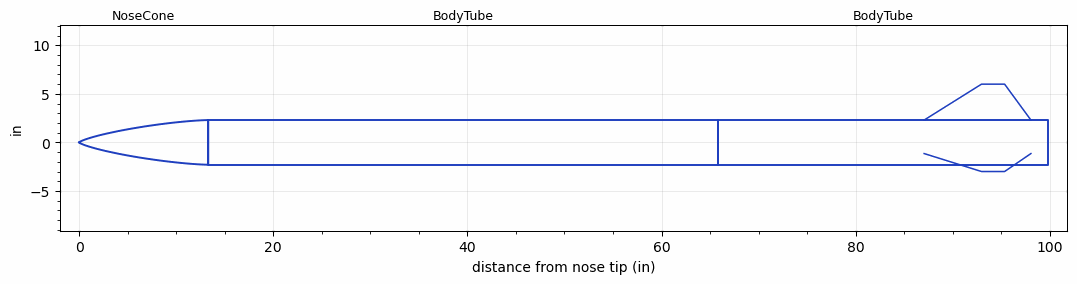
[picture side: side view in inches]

<RASAeroDocument>
 <FileVersion>2</FileVersion>
 <RocketDesign>
  <NoseCone>
   <Length>13.3</Length>
   <Diameter>4.6</Diameter>
   <Shape>Von Karman Ogive</Shape>
   <Location>0</Location>
  </NoseCone>
  <BodyTube>
   <Length>52.5</Length>
   <Diameter>4.6</Diameter>
   <Location>13.3</Location>
  </BodyTube>
  <BodyTube>
   <Length>34</Length>
   <Diameter>4.6</Diameter>
   <RailGuideDiameter>0.5</RailGuideDiameter>
   <RailGuideHeight>0.5</RailGuideHeight>
   <Location>65.8</Location>
   <Fin>
    <Count>3</Count>
    <Chord>11</Chord>
    <Span>3.7</Span>
    <SweepDistance>5.91</SweepDistance>
    <TipChord>2.38</TipChord>
    <Thickness>0.3</Thickness>
    <Location>12.75</Location>
    <AirfoilSection>Subsonic NACA</AirfoilSection>
   </Fin>
  </BodyTube>
  <Surface>Smooth (Zero Roughness)</Surface>
  <ModifiedBarrowman>False</ModifiedBarrowman>
  <Turbulence>False</Turbulence>
  <UseBooster1>False</UseBooster1>
  <UseBooster2>False</UseBooster2>
 </RocketDesign>
 <LaunchSite>
  <Altitude>4593</Altitude>
  <Pressure>25.4</Pressure>
  <RodAngle>6</RodAngle>
  <RodLength>15</RodLength>
  <Temperature>100</Temperature>
  <WindSpeed>0</WindSpeed>
 </LaunchSite>
 <Recovery>
  <Altitude1>1000</Altitude1>
  <Altitude2>1500</Altitude2>
  <DeviceType1>Parachute</DeviceType1>
  <DeviceType2>Parachute</DeviceType2>
  <Event1>True</Event1>
  <Event2>True</Event2>
  <Size1>33</Size1>
  <Size2>120</Size2>
  <EventType1>Apogee</EventType1>
  <EventType2>Altitude</EventType2>
  <CD1>1.33</CD1>
  <CD2>2.2</CD2>
 </Recovery>
 <SimulationList>
  <Simulation>
   <SustainerEngine>L1685-SS  (CTI)</SustainerEngine>
   <SustainerLaunchWt>39</SustainerLaunchWt>
   <SustainerNozzleDiameter>1.5</SustainerNozzleDiameter>
   <SustainerCG>57.5</SustainerCG>
   <SustainerIgnitionDelay>0</SustainerIgnitionDelay>
   <Booster1SeparationDelay>0</Booster1SeparationDelay>
   <Booster1IgnitionDelay>0</Booster1IgnitionDelay>
   <IncludeBooster1>False</IncludeBooster1>
   <Booster2Delay>0</Booster2Delay>
   <IncludeBooster2>False</IncludeBooster2>
   <TimetoApogee>25.8405</TimetoApogee>
   <MaxAltitude>10922.85</MaxAltitude>
   <MaxVelocity>937.4421</MaxVelocity>
  </Simulation>
 </SimulationList>
</RASAeroDocument>
